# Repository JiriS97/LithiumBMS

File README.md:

# LithiumBMS
This project is 1-6S Li-Ion/Li-Pol Battery management system, with balancer, load switch
and advanced features as external monitoring/setting over UART and temperature measurement
Development of this board began for BUT (VUT Brno in Czech), on Robotics course.

It also includes configurator app, which can be found in [this repo](https://github.com/JiriS97/LithiumBMS-Configurator).

## Supported batteries
All Li-Ion and Li-Pol batteries of 1-6 serially connected cells

## Parameters
| Parameter                                              |     Value    | Unit |
|--------------------------------------------------------|:------------:|:----:|
| Dimmensions                                            |   65x40x21   |  mm  |
| Maximal number of cells                                |       6      |   -  |
| Minimal number of cells                                |       1      |   -  |
| Maximal voltage of entire accupack                     |      26      |   V  |
| Maximal voltage per single cell                        |       6      |   V  |
| Maximal pulse current with this configuration          |      30      |   A  |
| Maximal current of WAGO connector                      |      16      |   A  |
| Maximal current of MOSFETs                             |      100     |   A  |
| Balancing current                                      |    60 ÷ 80   |  mA  |
| Peak power consumption                                 |       5      |  mA  |
| Idle power consumption                                 |      120     |  uA  |
| Typical consumed current when measuring U, I, P        |       2      |  mA  |
| Typical consumed power when measuring voltage of cells |       4      |  uA  |
| Typical average power consumption                      |      200     |  uA  |
| Typical current drain from cell that is being balanced |      70      |  mA  |
| Typical power drain from cell that is being balanced   |      200     |  mW  |
| Operating temperature range                            |   -20 ÷ +80  |  °C  |
| Storing temperature range                              |  -20 ÷ +100  |  °C  |
| Internal resistance of saturated power MOSFETs         |      4,5     |  mΩ  |
| Total internal resistance when MOSFEts are saturated   |       9      |  mΩ  |
| Period of cell voltage measurement                     | configurable |  ms  |
| Period of voltage, power and current measurement       | configurable |  ms  |
| Time of microcontroller sleep state                    | configurable |  ms  |

Detailed description of supported AT commands and the board itself can be found in attached PDF documents in the [Docs folder](Docs),
schematic and PCB layout in the [PCB folder](PCB)

## License
This project is licensed under the MIT License - see the [LICENSE.md](LICENSE.md) file for details

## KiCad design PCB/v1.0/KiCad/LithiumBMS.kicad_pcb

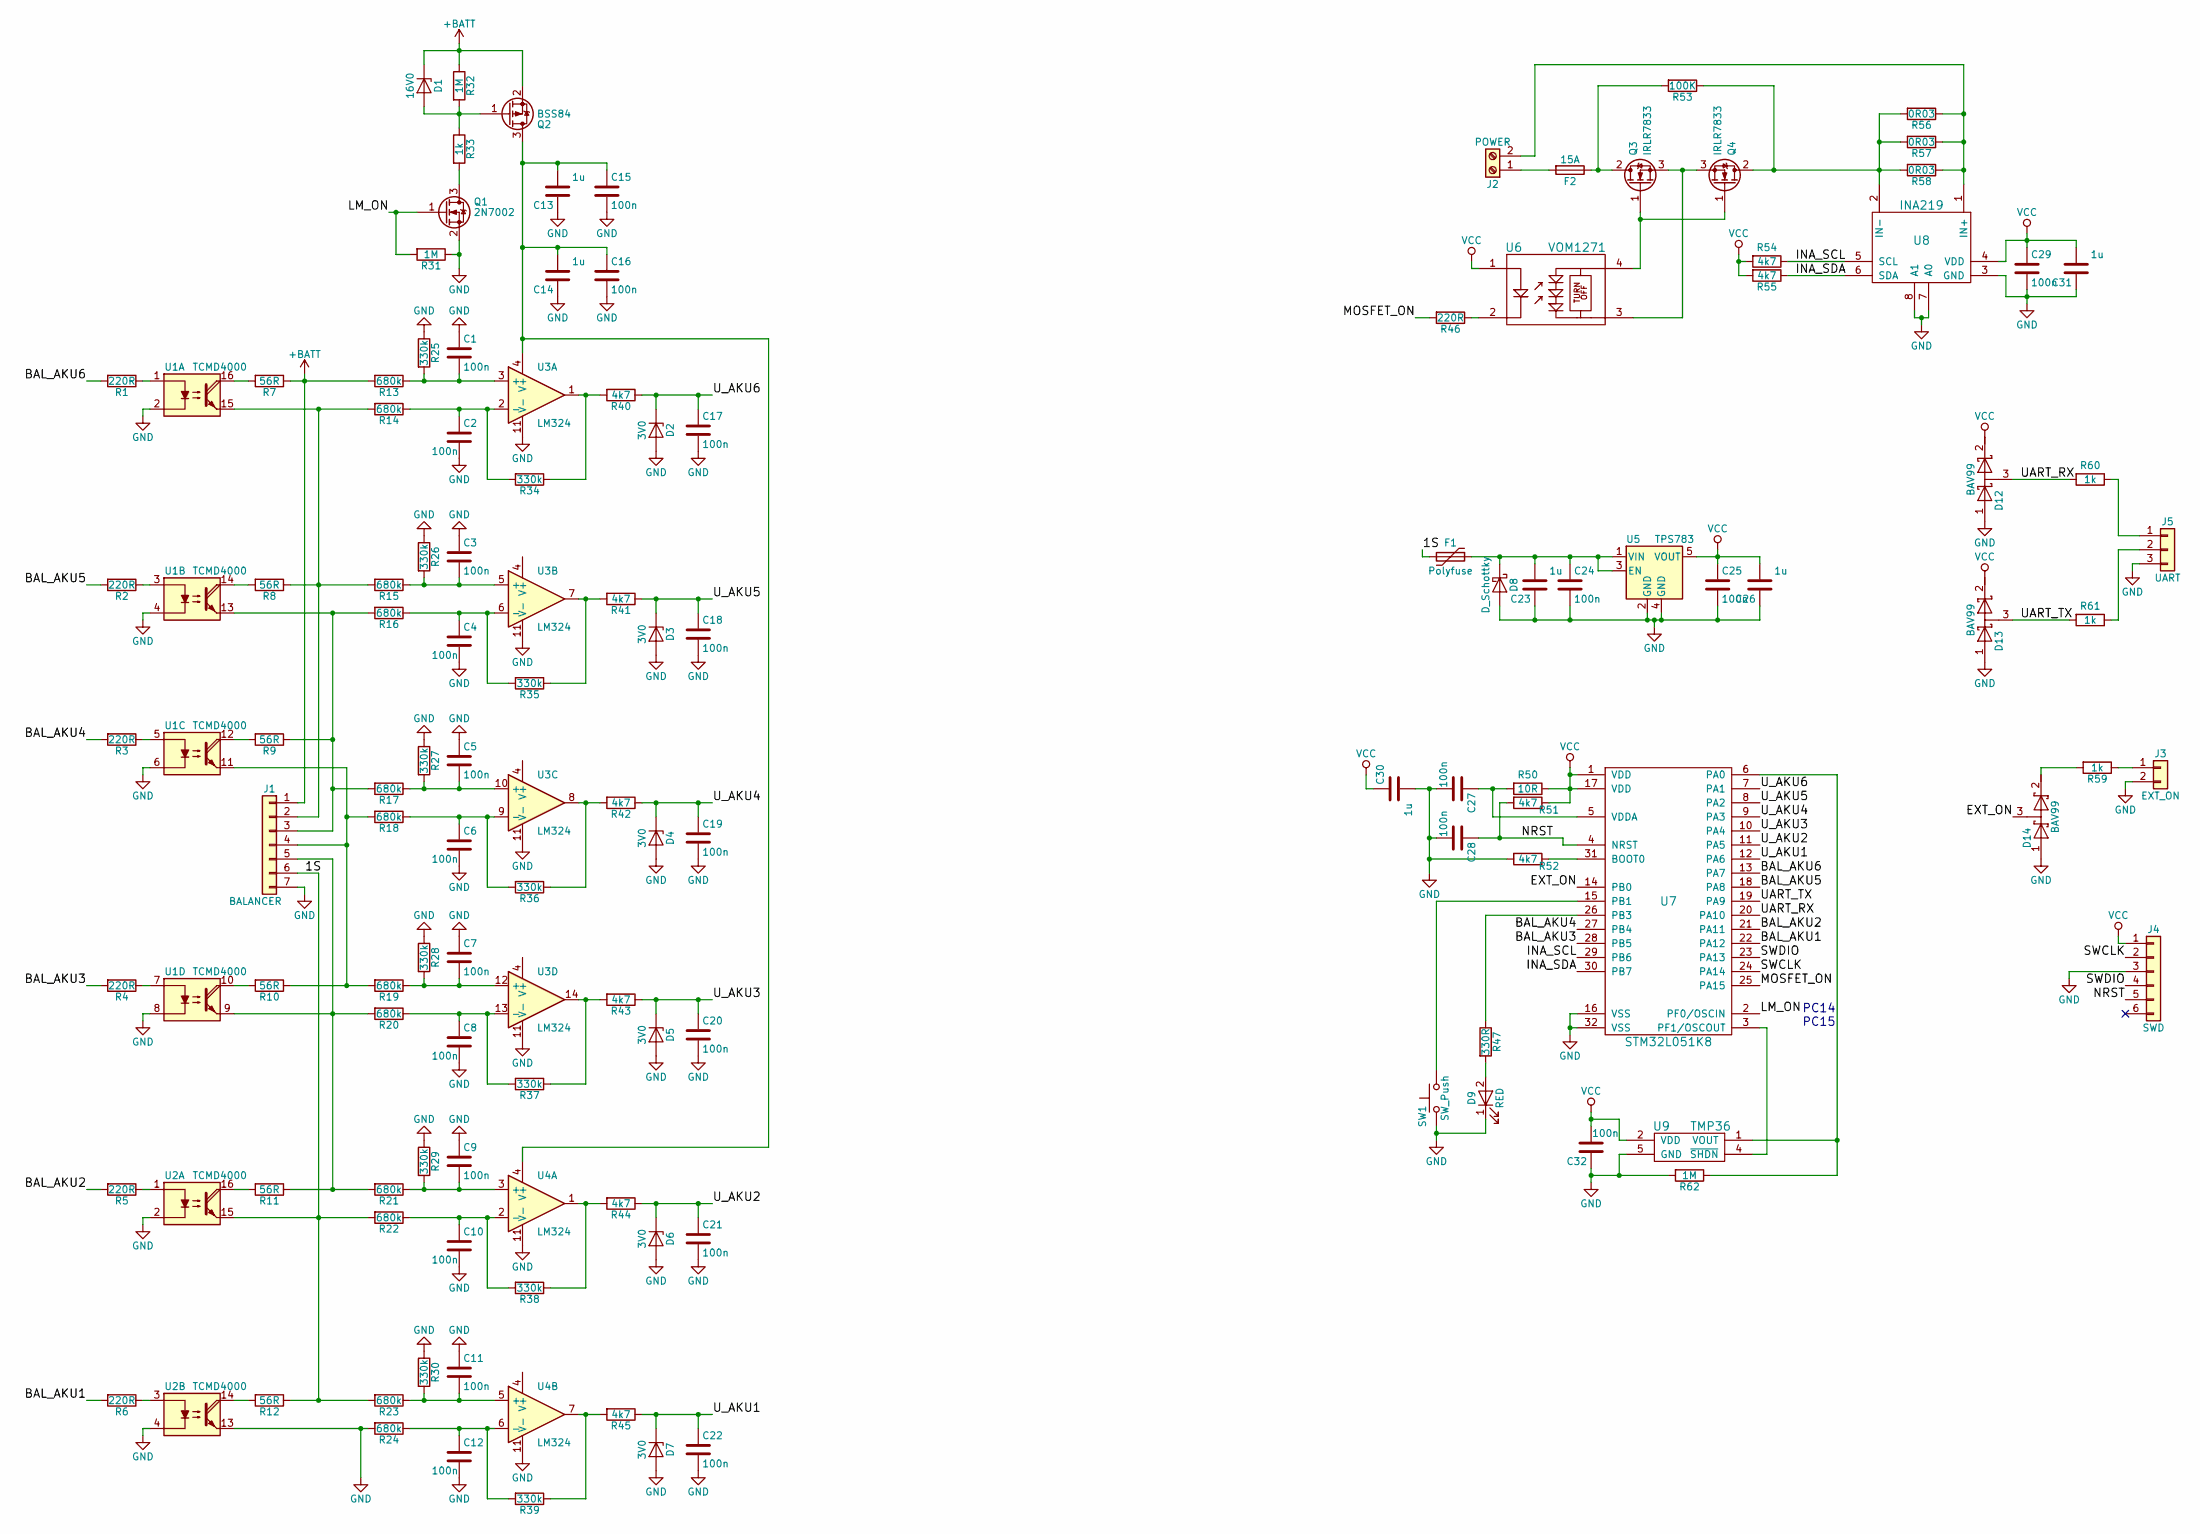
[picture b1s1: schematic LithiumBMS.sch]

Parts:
C1, C2, C3, C4, C5, C6, C7, C8, C9, C10, C11, C12, C15, C16, C17, C18, C19, C20, C21, C22, C24, C25, C27, C28, C29, C32: 100n; C_0603
C13, C14, C23, C26, C30, C31: 1u; C_0603
D1: 16V0; D_MiniMELF
D2, D3, D4, D5, D6, D7: 3V0; D_MiniMELF
D8: D_Schottky; D_SMA
D9: RED; LED_0603
D12, D13, D14: BAV99; SOT-23
F1: Polyfuse; R_1812
F2: 15A; BladeFuse-Mini_Keystone_3568
J1: BALANCER; JST_EH_B07B-EH-A_07x2.50mm_Straight
J2: POWER; TerminalBlock_WAGO-804_RM5mm_2pol
J3: EXT_ON; Pin_Header_Straight_1x02_Pitch2.54mm
J4: SWD; Pin_Header_Straight_1x06_Pitch2.54mm
J5: UART; Pin_Header_Straight_1x03_Pitch2.54mm
Q1: 2N7002; SOT-23
Q2: BSS84; SOT-23
Q3, Q4: IRLR7833; TO-252-2
R1, R2, R3, R4, R5, R6, R46: 220R; R_0603
R7, R8, R9, R10, R11, R12: 56R; R_2512
R13, R14, R15, R16, R17, R18, R19, R20, R21, R22, R23, R24: 680k; R_0603
R25, R26, R27, R28, R29, R30, R34, R35, R36, R37, R38, R39: 330k; R_0603
R31, R32, R62: 1M; R_0603
R33, R59, R60, R61: 1k; R_0603
R40, R41, R42, R43, R44, R45, R51, R52, R54, R55: 4k7; R_0603
R47: 330R; R_0603
R50: 10R; R_0603
R53: 100K; R_0603
R56, R57, R58: 0R03; R_1206
SW1: SW_Push; Button_SMD_5.2mm
U1, U2: TCMD4000; SOP-16_4.4x10.4mm_Pitch1.27mm
U3, U4: LM324; SOIC-14_3.9x8.7mm_Pitch1.27mm
U5: TPS783; SOT-23-5
U6: VOM1271; SOP-4_3.8x4.1mm_Pitch2.54mm
U7: STM32L051K8; LQFP-32_7x7mm_Pitch0.8mm
U8: INA219; SOT-23-8
U9: TMP36; SOT-23-5

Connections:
+BATT: D1.1 (K), J1.1, Q2.2 (S), R7.1, R13.2, R32.1
/1S: F1.2, J1.6, R12.1, R22.2, R23.2, U2.15
/BAL_AKU1: R6.2, U7.22 (PA12)
/BAL_AKU2: R5.2, U7.21 (PA11)
/BAL_AKU3: R4.2, U7.28 (PB5)
/BAL_AKU4: R3.2, U7.27 (PB4)
/BAL_AKU5: R2.2, U7.18 (PA8)
/BAL_AKU6: R1.2, U7.13 (PA7)
/EXT_ON: D14.3 (common), U7.14 (PB0)
/INA_SCL: R54.1, U7.29 (PB6), U8.5 (SCL)
/INA_SDA: R55.1, U7.30 (PB7), U8.6 (SDA)
/LM_ON: Q1.1 (G), R31.2, U7.2 (PF0/OSCIN)
/MOSFET_ON: R46.2, U7.25 (PA15)
/NRST: C28.1, J4.5, R51.2, U7.4 (NRST)
/SWCLK: J4.2, U7.24 (PA14)
/SWDIO: J4.4, U7.23 (PA13)
/UART_RX: D12.3 (common), R60.2, U7.20 (PA10)
/UART_TX: D13.3 (common), R61.2, U7.19 (PA9)
/U_AKU1: C22.1, D7.1 (K), R45.1, U7.12 (PA6)
/U_AKU2: C21.1, D6.1 (K), R44.1, U7.11 (PA5)
/U_AKU3: C20.1, D5.1 (K), R43.1, U7.10 (PA4)
/U_AKU4: C19.1, D4.1 (K), R42.1, U7.9 (PA3)
/U_AKU5: C18.1, D3.1 (K), R41.1, U7.8 (PA2)
/U_AKU6: C17.1, D2.1 (K), R40.1, U7.7 (PA1)
GND: C1.1, C2.2, C3.1, C4.2, C5.1, C6.2, C7.1, C8.2, C9.1, C10.2, C11.1, C12.2, C13.1, C14.1, C15.2, C16.2, C17.2, C18.2, C19.2, C20.2, C21.2, C22.2, C23.1, C24.2, C25.2, C26.1, C27.2, C28.2, C29.2, C30.2, C31.1, C32.1, D2.2 (A), D3.2 (A), D4.2 (A), D5.2 (A), D6.2 (A), D7.2 (A), D8.2 (A), D9.1 (K), D12.1 (A), D13.1 (A), D14.1 (A), J1.7, J3.2, J4.3, J5.3, Q1.2 (S), R24.2, R25.1, R26.1, R27.1, R28.1, R29.1, R30.1, R31.1, R52.2, R62.2, SW1.2, U1.2, U1.4, U1.6, U1.8, U2.2, U2.4, U2.13, U3.11 (V-), U4.11 (V-), U5.2 (GND), U5.4 (GND), U7.16 (VSS), U7.32 (VSS), U8.3 (GND), U8.7 (A0), U8.8 (A1), U9.5 (GND)
unnamed: C1.2, R13.1, R25.2, U3.3 (+)
unnamed: C2.1, R14.1, R34.2, U3.2 (-)
unnamed: C3.2, R15.1, R26.2, U3.5 (+)
unnamed: C4.1, R16.1, R35.2, U3.6 (-)
unnamed: C5.2, R17.1, R27.2, U3.10 (+)
unnamed: C6.1, R18.1, R36.2, U3.9 (-)
unnamed: C7.2, R19.1, R28.2, U3.12 (+)
unnamed: C8.1, R20.1, R37.2, U3.13 (-)
unnamed: C9.2, R21.1, R29.2, U4.3 (+)
unnamed: C10.1, R22.1, R38.2, U4.2 (-)
unnamed: C11.2, R23.1, R30.2, U4.5 (+)
unnamed: C12.1, R24.1, R39.2, U4.6 (-)
unnamed: C13.2, C14.2, C15.1, C16.1, Q2.3 (D), U3.4 (V+), U4.4 (V+)
unnamed: C23.2, C24.1, D8.1 (K), F1.1, U5.1 (VIN), U5.3 (EN)
unnamed: C27.1, R50.2, U7.5 (VDDA)
unnamed: D1.2 (A), Q2.1 (G), R32.2, R33.1
unnamed: D9.2 (A), R47.2
unnamed: D14.2 (K), R59.2
unnamed: F2.1, Q3.2 (D), R53.2
unnamed: F2.2, J2.1
unnamed: J1.2, R8.1, R14.2, R15.2, U1.15
unnamed: J1.3, R9.1, R16.2, R17.2, U1.13
unnamed: J1.4, R10.1, R18.2, R19.2, U1.11
unnamed: J1.5, R11.1, R20.2, R21.2, U1.9
unnamed: J2.2, R56.1, R57.1, R58.1, U8.1 (IN+)
unnamed: J3.1, R59.1
unnamed: J5.1, R60.1
unnamed: J5.2, R61.1
unnamed: Q1.3 (D), R33.2
unnamed: Q3.1 (G), Q4.1 (G), U6.4
unnamed: Q3.3 (S), Q4.3 (S), U6.3
unnamed: Q4.2 (D), R53.1, R56.2, R57.2, R58.2, U8.2 (IN-)
unnamed: R1.1, U1.1
unnamed: R2.1, U1.3
unnamed: R3.1, U1.5
unnamed: R4.1, U1.7
unnamed: R5.1, U2.1
unnamed: R6.1, U2.3
unnamed: R7.2, U1.16
unnamed: R8.2, U1.14
unnamed: R9.2, U1.12
unnamed: R10.2, U1.10
unnamed: R11.2, U2.16
unnamed: R12.2, U2.14
unnamed: R34.1, R40.2, U3.1
unnamed: R35.1, R41.2, U3.7
unnamed: R36.1, R42.2, U3.8
unnamed: R37.1, R43.2, U3.14
unnamed: R38.1, R44.2, U4.1
unnamed: R39.1, R45.2, U4.7
unnamed: R46.1, U6.2
unnamed: R47.1, U7.26 (PB3)
unnamed: R52.1, U7.31 (BOOT0)
unnamed: R62.1, U7.6 (PA0), U9.1 (VOUT)
unnamed: SW1.1, U7.15 (PB1)
unnamed: U7.3 (PF1/OSCOUT), U9.4 (~SHDN)
VCC: C25.1, C26.2, C29.1, C30.1, C31.2, C32.2, D12.2 (K), D13.2 (K), J4.1, R50.1, R51.1, R54.2, R55.2, U5.5 (VOUT), U6.1, U7.1 (VDD), U7.17 (VDD), U8.4 (VDD), U9.2 (VDD)

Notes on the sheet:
PC14 PC15

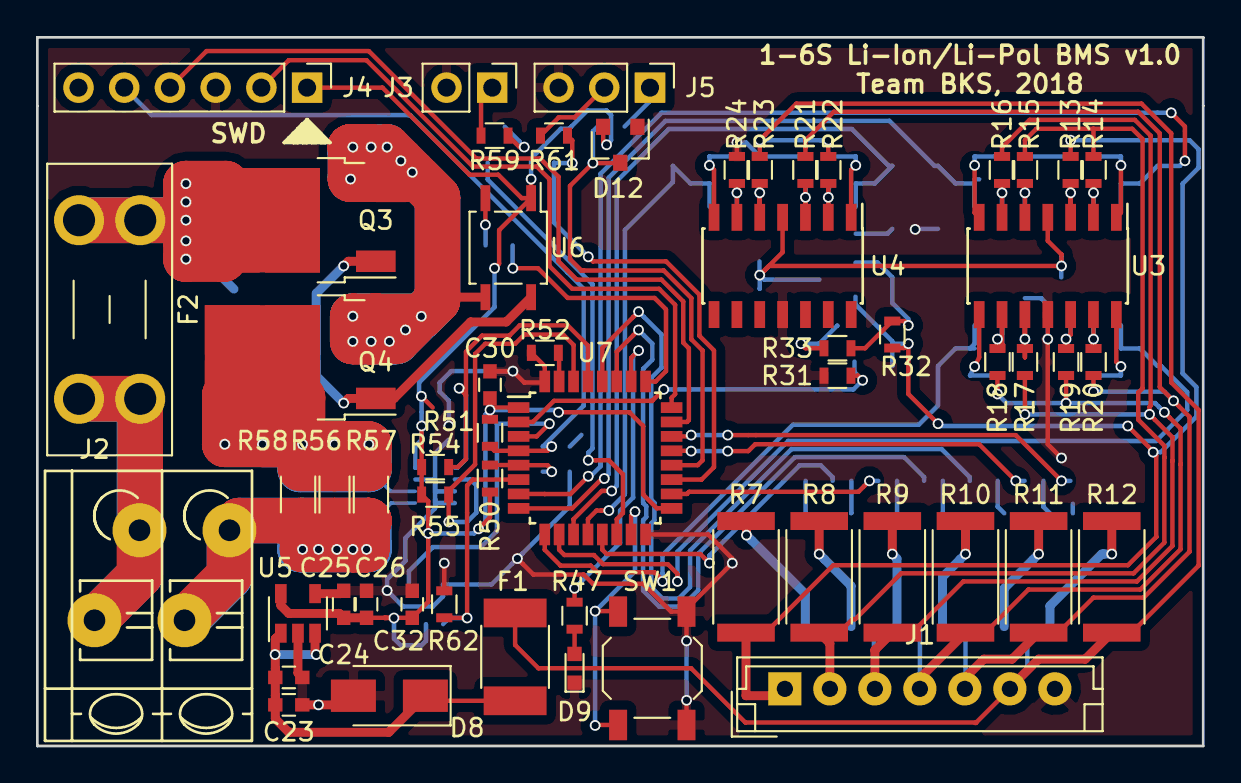
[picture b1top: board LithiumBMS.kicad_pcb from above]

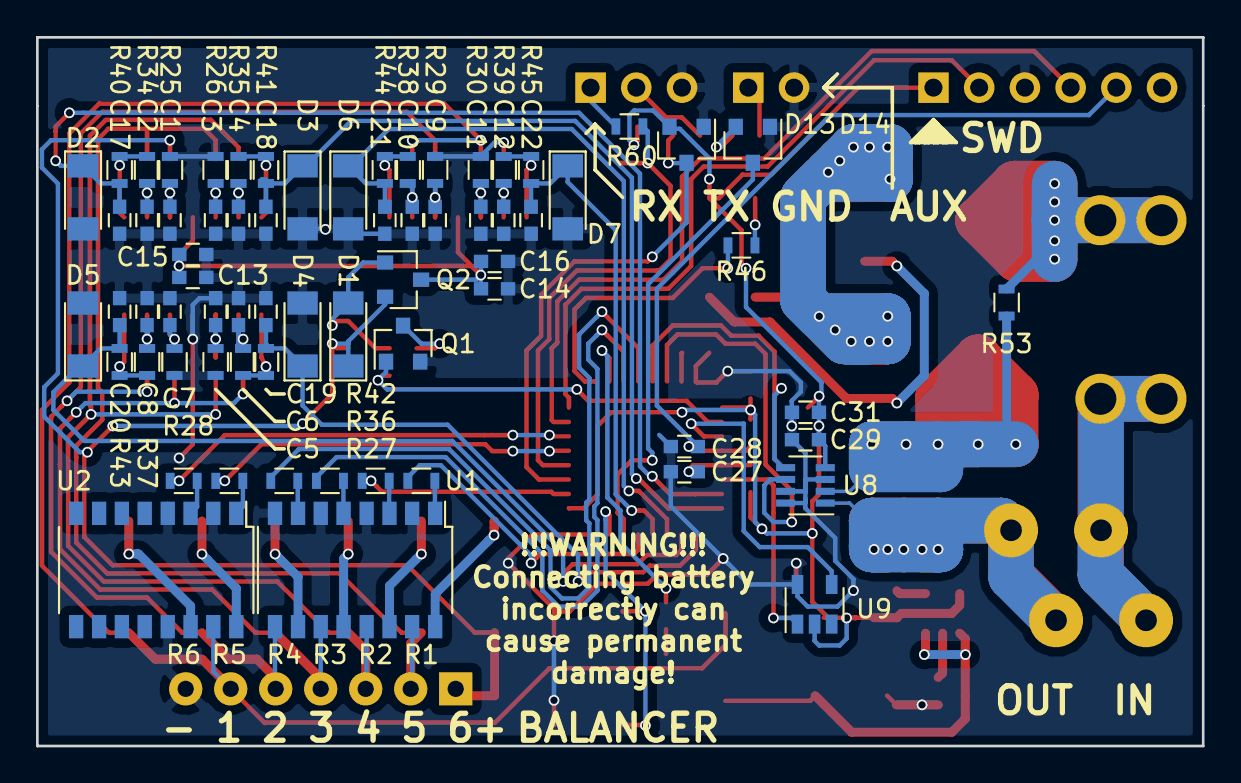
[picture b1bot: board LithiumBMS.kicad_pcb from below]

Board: 2 copper layers, 64.8 x 39.4 mm, 125 parts (68 on the bottom side), 82 nets.

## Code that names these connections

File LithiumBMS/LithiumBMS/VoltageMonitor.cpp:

#include  "VoltageMonitor.h"

VoltageMonitor::VoltageMonitor()
	: OpAmpPower_(PC14)
	, tempNShdn_(PC15) {
	PeriphUtils::EnableClock(ADC1);
	GpioPin(PA0).Analog();       //temp
	GpioPin(PA1).Analog();       //aku1..6
	GpioPin(PA2).Analog();
	GpioPin(PA3).Analog();
	GpioPin(PA4).Analog();
	GpioPin(PA5).Analog();
	GpioPin(PA6).Analog();
	OpAmpPower_.Output();
	tempNShdn_.Output();
	OpAmpPower_ = 0;  	//shutdown all analog periphs
	tempNShdn_ = 0;
	Delay::Init();

	adcHandle_.Instance = ADC1;

	adcHandle_.Init.OversamplingMode = DISABLE;

	adcHandle_.Init.ClockPrescaler = ADC_CLOCK_SYNC_PCLK_DIV1;
	adcHandle_.Init.LowPowerAutoPowerOff = ENABLE;
	adcHandle_.Init.LowPowerFrequencyMode = DISABLE;
	adcHandle_.Init.LowPowerAutoWait = ENABLE;

	adcHandle_.Init.Resolution = ADC_RESOLUTION_12B;
	adcHandle_.Init.SamplingTime = ADC_SAMPLETIME_79CYCLES_5;
	adcHandle_.Init.ScanConvMode = ADC_SCAN_DIRECTION_BACKWARD;
	adcHandle_.Init.DataAlign = ADC_DATAALIGN_RIGHT;
	adcHandle_.Init.ContinuousConvMode = DISABLE;
	adcHandle_.Init.DiscontinuousConvMode = DISABLE;
	adcHandle_.Init.ExternalTrigConvEdge = ADC_EXTERNALTRIGCONVEDGE_NONE;
	adcHandle_.Init.EOCSelection = ADC_EOC_SINGLE_CONV;
	adcHandle_.Init.DMAContinuousRequests = DISABLE;

	HAL_ADC_Init(&adcHandle_);
	HAL_ADCEx_Calibration_Start(&adcHandle_, ADC_SINGLE_ENDED);

	ADC_ChannelConfTypeDef chConfig;
	chConfig.Channel = ADC_CHANNEL_0;      //temp
	HAL_ADC_ConfigChannel(&adcHandle_, &chConfig);

	chConfig.Channel = ADC_CHANNEL_1;  	 //accu
	HAL_ADC_ConfigChannel(&adcHandle_, &chConfig);
	chConfig.Channel = ADC_CHANNEL_2;
	HAL_ADC_ConfigChannel(&adcHandle_, &chConfig);
	chConfig.Channel = ADC_CHANNEL_3;
	HAL_ADC_ConfigChannel(&adcHandle_, &chConfig);
	chConfig.Channel = ADC_CHANNEL_4;
	HAL_ADC_ConfigChannel(&adcHandle_, &chConfig);
	chConfig.Channel = ADC_CHANNEL_5;
	HAL_ADC_ConfigChannel(&adcHandle_, &chConfig);
	chConfig.Channel = ADC_CHANNEL_6;
	HAL_ADC_ConfigChannel(&adcHandle_, &chConfig);
}

void VoltageMonitor::UpdateAll() {
	OpAmpPower_ = 1;
	tempNShdn_ = 1;
	Delay::Ms(2);

	HAL_ADC_Start(&adcHandle_);
	for (int i = 0; i < 7; i++) {
		HAL_ADC_PollForConversion(&adcHandle_, 10);
		if ((HAL_ADC_GetState(&adcHandle_) & HAL_ADC_STATE_REG_EOC) == HAL_ADC_STATE_REG_EOC) {
			voltages_[i] = (HAL_ADC_GetValue(&adcHandle_)*ADC_VDD) / 4096.0;
			if (i != 6) voltages_[i] *= 2.0606; //0-5 aku, 6 temperature sensor
		}
	}

	OpAmpPower_ = 0;
	tempNShdn_ = 0;
}


uint16_t VoltageMonitor::GetCellMV(int id) {
	return voltages_[id]; //0-5 aku
}


float VoltageMonitor::GetTempDegC() {
	return (voltages_[6] - 500) / 10.0; //(voltage[mV] - 500)/10
}

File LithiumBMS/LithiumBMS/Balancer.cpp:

#include "Balancer.h"

Balancer::Balancer()
	: pins_{ PA12, PA11, PB5, PB4, PA8, PA7 }
{
	for (int i = 0; i < 6; i++)
	{
		pins_[i].Output();
		pins_[i] = 0;
	}	
}

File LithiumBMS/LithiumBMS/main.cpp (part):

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#include <cmath>

//pins
GpioPin ExtOn(PB0, PinMode::INPUT);
GpioPin Button(PB1, PinMode::INPUT);
GpioPin Led(PB3, PinMode::OUTPUT);
GpioPin PowerSwitch(PA15, PinMode::OUTPUT);

//global objects
Communication SerialLink;
LowPowerTimer WakeupTimer;
I2cHardware InaBus(I2C1, PB6, PB7, 1, 0x00B1112E);
INA219 Monitor(InaBus);
Balancer BatteryBalancer;
VoltageMonitor BatteryMonitor;
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
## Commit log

2018-05-10 Everything works fine, added Readme and License, updated documentation
2018-05-10 Updated readme.
